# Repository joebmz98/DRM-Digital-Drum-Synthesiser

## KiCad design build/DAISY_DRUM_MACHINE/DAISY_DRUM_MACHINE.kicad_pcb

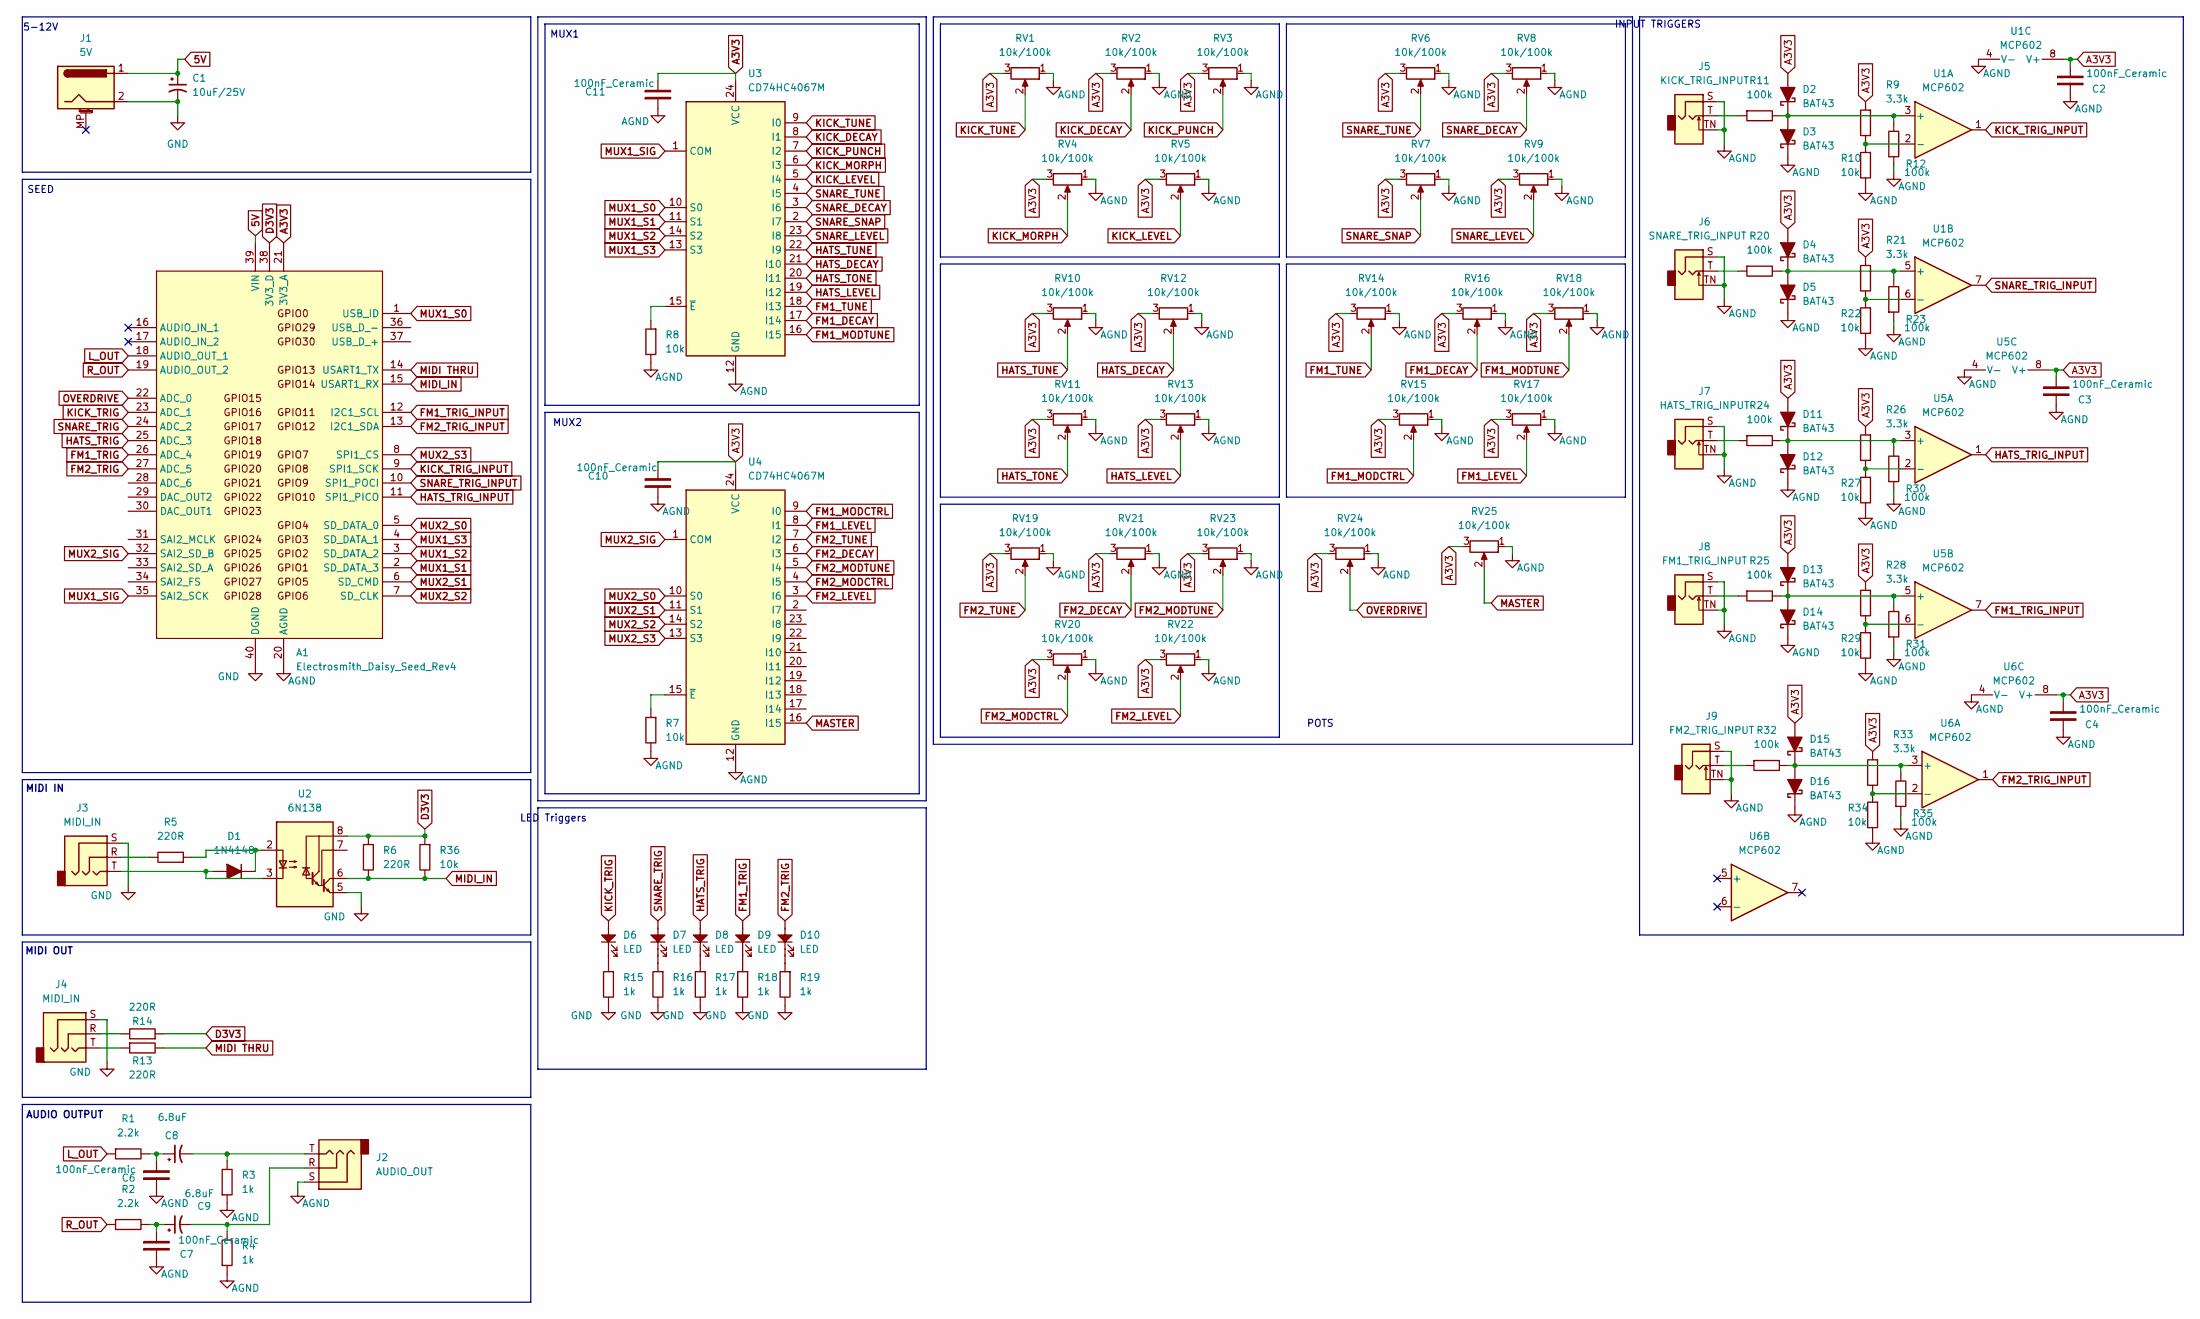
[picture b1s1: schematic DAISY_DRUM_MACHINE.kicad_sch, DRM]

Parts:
A1: Electrosmith_Daisy_Seed_Rev4; Electrosmith_Daisy_Seed
C1: 10uF_4x5.3_10V; CP_Radial_D4.0mm_P1.50mm; Part Number EEE-FN1A100R; JLCPCB ID C176661
C2, C3, C4, C6, C7, C10, C11: 100nF_Ceramic; C_0603_1608Metric_Pad1.08x0.95mm_HandSolder
C8, C9: 6.8uF; CP_Radial_D4.0mm_P1.50mm; Part Number EEE-FN1A100R; JLCPCB ID C176661
D1: 1N4148; D_0603_1608Metric_Pad1.05x0.95mm_HandSolder
D2, D3, D4, D5, D11, D12, D13, D14, D15, D16: BAT43; D_DO-35_SOD27_P7.62mm_Horizontal
D6, D7, D8, D9, D10: LED; LED_D5.0mm
J1: 5V; BarrelJack_GCT_DCJ200-10-A_Horizontal
J2: AUDIO_OUT; Jack_3.5mm_CUI_SJ1-3525N_Horizontal
J3, J4: MIDI_IN; Jack_3.5mm_CUI_SJ1-3525N_Horizontal
J5: KICK_TRIG_INPUT; Jack_3.5mm_CUI_SJ1-3525N_Horizontal
J6: SNARE_TRIG_INPUT; Jack_3.5mm_CUI_SJ1-3525N_Horizontal
J7: HATS_TRIG_INPUT; Jack_3.5mm_CUI_SJ1-3525N_Horizontal
J8: FM1_TRIG_INPUT; Jack_3.5mm_CUI_SJ1-3525N_Horizontal
J9: FM2_TRIG_INPUT; Jack_3.5mm_CUI_SJ1-3525N_Horizontal
R1, R2: 2.2k; R_0603_1608Metric_Pad0.98x0.95mm_HandSolder
R3, R4, R15, R16, R17, R18, R19: 1k; R_0603_1608Metric_Pad0.98x0.95mm_HandSolder
R5, R6, R13, R14: 220R; R_0603_1608Metric_Pad0.98x0.95mm_HandSolder
R7, R8, R10, R22, R27, R29, R34, R36: 10k; R_0603_1608Metric_Pad0.98x0.95mm_HandSolder
R9, R21, R26, R28, R33: 3.3k; R_0603_1608Metric_Pad0.98x0.95mm_HandSolder
R11, R12, R20, R23, R24, R25, R30, R31, R32, R35: 100k; R_0603_1608Metric_Pad0.98x0.95mm_HandSolder
RV1, RV2, RV3, RV4, RV5, RV6, RV7, RV8, RV9, RV10, RV11, RV12, RV13, RV14, RV15, RV16, RV17, RV18, RV19, RV20, RV21, RV22, RV23, RV24, RV25: 10k/100k; Potentiometer_Alpha_RD901F-40-00D_Single_Vertical
U1, U5, U6: MCP602; SOIC-8_3.9x4.9mm_P1.27mm
U2: 6N138; DIP-8_W7.62mm_LongPads
U3, U4: CD74HC4067M; SOIC-24W_7.5x15.4mm_P1.27mm

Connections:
5V: A1.39 (VIN), C1.1, J1.1
A3V3: A1.21 (3V3_A), C2.2, C3.2, C4.2, C10.2, C11.2, D2.2 (A), D4.2 (A), D11.2 (A), D13.2 (A), D15.2 (A), R9.1, R21.1, R26.1, R28.1, R33.1, RV1.3, RV2.3, RV3.3, RV4.3, RV5.3, RV6.3, RV7.3, RV8.3, RV9.3, RV10.3, RV11.3, RV12.3, RV13.3, RV14.3, RV15.3, RV16.3, RV17.3, RV18.3, RV19.3, RV20.3, RV21.3, RV22.3, RV23.3, RV24.3, RV25.3, U1.8 (V+), U3.24 (VCC), U4.24 (VCC), U5.8 (V+), U6.8 (V+)
AGND: A1.20 (AGND), C2.1, C3.1, C4.1, C6.1, C7.1, C10.1, C11.1, D3.1 (K), D5.1 (K), D12.1 (K), D14.1 (K), D16.1 (K), J2.S, J5.S, J5.TN, J6.S, J6.TN, J7.S, J7.TN, J8.S, J8.TN, J9.S, J9.TN, R3.1, R4.1, R7.2, R8.2, R10.2, R12.1, R22.2, R23.1, R27.2, R29.2, R30.1, R31.1, R34.2, R35.1, RV1.1, RV2.1, RV3.1, RV4.1, RV5.1, RV6.1, RV7.1, RV8.1, RV9.1, RV10.1, RV11.1, RV12.1, RV13.1, RV14.1, RV15.1, RV16.1, RV17.1, RV18.1, RV19.1, RV20.1, RV21.1, RV22.1, RV23.1, RV24.1, RV25.1, U1.4 (V-), U3.12 (GND), U4.12 (GND), U5.4 (V-), U6.4 (V-)
D3V3: A1.38 (3V3_D), R6.1, R14.1, R36.1, U2.8 (VCC)
FM1_DECAY: RV16.2, U3.17 (I14)
FM1_LEVEL: RV17.2, U4.8 (I1)
FM1_MODCTRL: RV15.2, U4.9 (I0)
FM1_MODTUNE: RV18.2, U3.16 (I15)
FM1_TRIG: A1.26 (ADC_4), D9.2
FM1_TRIG_INPUT: A1.12 (I2C1_SCL), U5.7
FM1_TUNE: RV14.2, U3.18 (I13)
FM2_DECAY: RV21.2, U4.6 (I3)
FM2_LEVEL: RV22.2, U4.3 (I6)
FM2_MODCTRL: RV20.2, U4.4 (I5)
FM2_MODTUNE: RV23.2, U4.5 (I4)
FM2_TRIG: A1.27 (ADC_5), D10.2
FM2_TRIG_INPUT: A1.13 (I2C1_SDA), U6.1
FM2_TUNE: RV19.2, U4.7 (I2)
GND: A1.40 (DGND), C1.2, J1.2, J3.S, J4.S, R15.2, R16.2, R17.2, R18.2, R19.2, U2.5 (GND)
HATS_DECAY: RV12.2, U3.21 (I10)
HATS_LEVEL: RV13.2, U3.19 (I12)
HATS_TONE: RV11.2, U3.20 (I11)
HATS_TRIG: A1.25 (ADC_3), D8.2
HATS_TRIG_INPUT: A1.11 (SPI1_PICO), U5.1
HATS_TUNE: RV10.2, U3.22 (I9)
KICK_DECAY: RV2.2, U3.8 (I1)
KICK_LEVEL: RV5.2, U3.5 (I4)
KICK_MORPH: RV4.2, U3.6 (I3)
KICK_PUNCH: RV3.2, U3.7 (I2)
KICK_TRIG: A1.23 (ADC_1), D6.2
KICK_TRIG_INPUT: A1.9 (SPI1_SCK), U1.1
KICK_TUNE: RV1.2, U3.9 (I0)
L_OUT: A1.18 (AUDIO_OUT_1), R1.1
MASTER: RV25.2, U4.16 (I15)
MIDI THRU: A1.14 (USART1_TX), R13.2
MIDI_IN: A1.15 (USART1_RX), R6.2, R36.2, U2.6 (VO2)
MUX1_S0: A1.1 (USB_ID), U3.10 (S0)
MUX1_S1: A1.2 (SD_DATA_3), U3.11 (S1)
MUX1_S2: A1.3 (SD_DATA_2), U3.14 (S2)
MUX1_S3: A1.4 (SD_DATA_1), U3.13 (S3)
MUX1_SIG: A1.35 (SAI2_SCK), U3.1 (COM)
MUX2_S0: A1.5 (SD_DATA_0), U4.10 (S0)
MUX2_S1: A1.6 (SD_CMD), U4.11 (S1)
MUX2_S2: A1.7 (SD_CLK), U4.14 (S2)
MUX2_S3: A1.8 (SPI1_CS), U4.13 (S3)
MUX2_SIG: A1.32 (SAI2_SD_B), U4.1 (COM)
unnamed: C6.2, C8.1, R1.2
unnamed: C7.2, C9.1, R2.2
unnamed: C8.2, J2.T, R3.2
unnamed: C9.2, J2.R, R4.2
unnamed: D1.2 (A), J3.T, U2.3 (C2)
unnamed: D1.1 (K), R5.1, U2.2 (C1)
unnamed: D2.1 (K), D3.2 (A), R11.2, R12.2, U1.3 (+)
unnamed: D4.1 (K), D5.2 (A), R20.2, R23.2, U1.5 (+)
unnamed: D6.1, R15.1
unnamed: D7.1, R16.1
unnamed: D8.1, R17.1
unnamed: D9.1, R18.1
unnamed: D10.1, R19.1
unnamed: D11.1 (K), D12.2 (A), R24.2, R30.2, U5.3 (+)
unnamed: D13.1 (K), D14.2 (A), R25.2, R31.2, U5.5 (+)
unnamed: D15.1 (K), D16.2 (A), R32.2, R35.2, U6.3 (+)
unnamed: J3.R, R5.2
unnamed: J4.R, R14.2
unnamed: J4.T, R13.1
unnamed: J5.T, R11.1
unnamed: J6.T, R20.1
unnamed: J7.T, R24.1
unnamed: J8.T, R25.1
unnamed: J9.T, R32.1
unnamed: R9.2, R10.1, U1.2 (-)
unnamed: R21.2, R22.1, U1.6 (-)
unnamed: R8.1, U3.15 (~E)
unnamed: R7.1, U4.15 (~E)
unnamed: R26.2, R27.1, U5.2 (-)
unnamed: R28.2, R29.1, U5.6 (-)
unnamed: R33.2, R34.1, U6.2 (-)
OVERDRIVE: A1.22 (ADC_0), RV24.2
R_OUT: A1.19 (AUDIO_OUT_2), R2.1
SNARE_DECAY: RV8.2, U3.3 (I6)
SNARE_LEVEL: RV9.2, U3.23 (I8)
SNARE_SNAP: RV7.2, U3.2 (I7)
SNARE_TRIG: A1.24 (ADC_2), D7.2
SNARE_TRIG_INPUT: A1.10 (SPI1_POCI), U1.7
SNARE_TUNE: RV6.2, U3.4 (I5)

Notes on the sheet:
MUX1
MIDI IN
LED Triggers
AUDIO OUTPUT
SEED
INPUT TRIGGERS
MUX2
MIDI OUT
5-12V
POTS

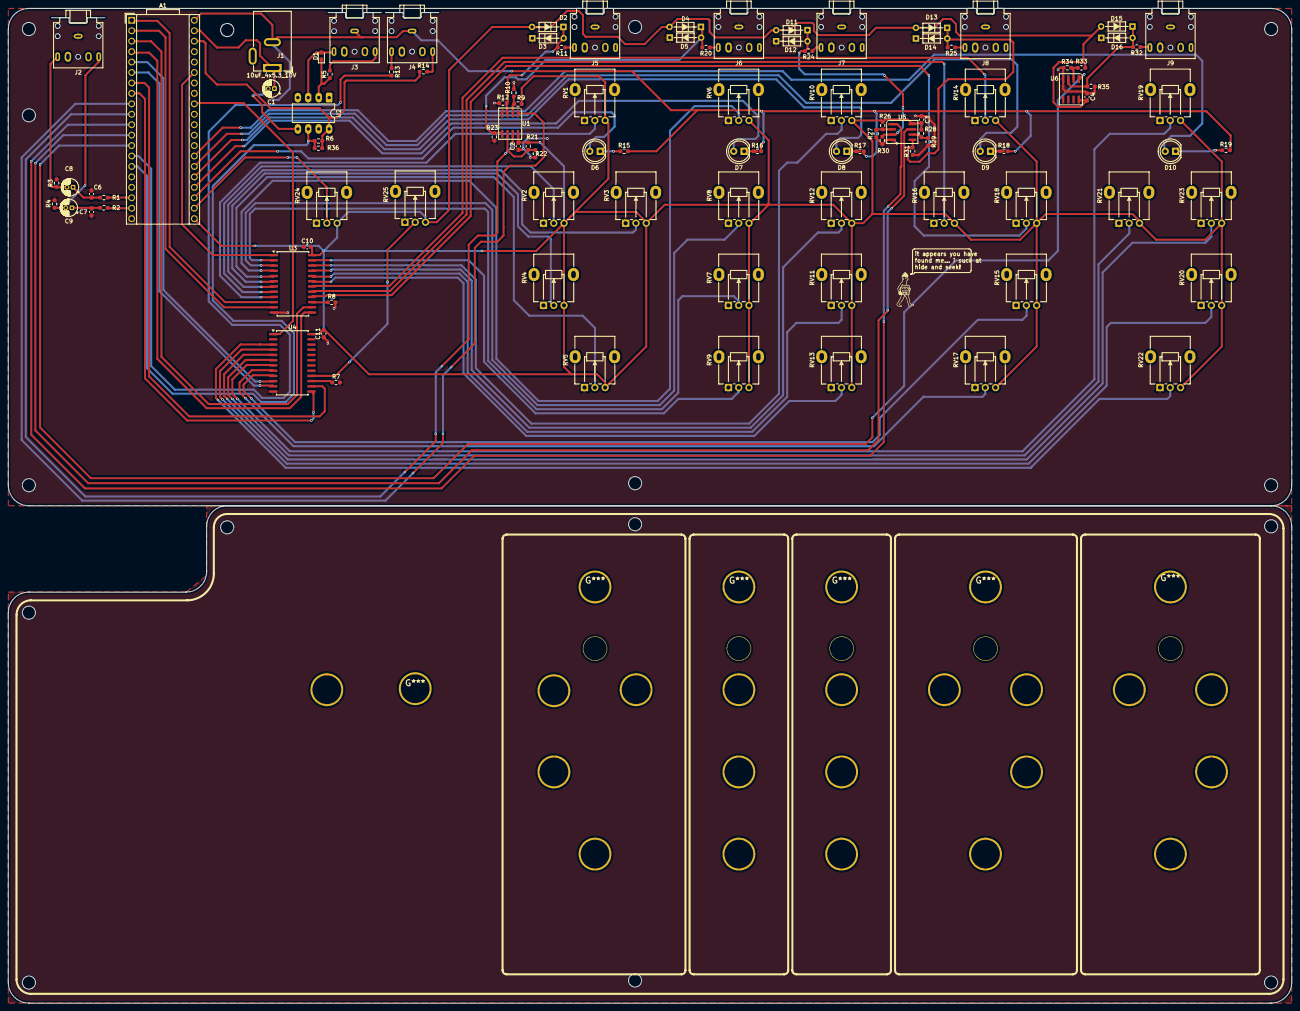
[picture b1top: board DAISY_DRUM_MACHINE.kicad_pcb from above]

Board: 2 copper layers, 312.2 x 242.0 mm, 103 parts (0 on the bottom side), 85 nets.

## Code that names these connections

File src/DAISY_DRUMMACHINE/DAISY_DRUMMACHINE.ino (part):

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
// MUX PINS
// MUX 1 -- S & SIG --
#define MUX1_S0 0
#define MUX1_S1 1
#define MUX1_S2 2
#define MUX1_S3 3
#define MUX1_SIG A11
// MUX 2 -- S & SIG --
#define MUX2_S0 4
#define MUX2_S1 5
#define MUX2_S2 6
#define MUX2_S3 7
#define MUX2_SIG A10

// MUX 1 CHANNEL DEFINITIONS
#define KICK_TUNE 0
#define KICK_DECAY 1
#define KICK_PUNCH 2
#define KICK_MORPH 3
#define KICK_LEVEL 4
#define SNARE_TUNE 5
#define SNARE_DECAY 6
#define SNARE_SNAP 7
#define SNARE_LEVEL 8
#define HATS_TUNE 9
#define HATS_DECAY 10
#define HATS_TONE 11
#define HATS_LEVEL 12
#define FM1_CARRIER_TUNE 13
#define FM1_DECAY 14
#define FM1_MODULATOR_TUNE 15

// MUX 2 CHANNEL DEFINITIONS
#define FM1_MOD_AMOUNT 0
#define FM1_LEVEL 1
#define FM2_CARRIER_TUNE 2
#define FM2_DECAY 3
#define FM2_MODULATOR_TUNE 4
#define FM2_MOD_AMOUNT 5
#define FM2_LEVEL 6
//#define SNARE_SNAP 7
//#define SNARE_LEVEL 8
//#define HATS_TUNE 9
//#define HATS_DECAY 10
//#define HATS_TONE 11
//#define HATS_LEVEL 12
//#define FM1_CARRIER_TUNE 13
//#define FM1_DECAY 14
#define MASTER_VOLUME 15

// TRIGGER/LED PINS
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
  // Setup MUX control pins as outputs
  // MUX 1
  pinMode(MUX1_S0, OUTPUT);
  pinMode(MUX1_S1, OUTPUT);
  pinMode(MUX1_S2, OUTPUT);
  pinMode(MUX1_S3, OUTPUT);
  pinMode(MUX1_SIG, INPUT);
  // MUX 2
  pinMode(MUX2_S0, OUTPUT);
  pinMode(MUX2_S1, OUTPUT);
  pinMode(MUX2_S2, OUTPUT);
  pinMode(MUX2_S3, OUTPUT);
  pinMode(MUX2_SIG, INPUT);

  // Setup direct pot pin
  pinMode(DISTORTION_POT, INPUT);
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void processValues() {

  // KICK POTS
  kickOscTune = fmap(muxValues[KICK_TUNE] / 65535.0f, 30.0, 120.0, Mapping::EXP);
  kickEnvDecay = fmap(muxValues[KICK_DECAY] / 65535.0f, 0.01, 1.5, Mapping::EXP);
  kickPunch = muxValues[KICK_PUNCH] / 65535.0f;  // 0.0 TO 1.0f
  kickMorph = muxValues[KICK_MORPH] / 65535.0f;  // 0.0 TO 1.0f
  kickLevel = fmap(muxValues[KICK_LEVEL] / 65535.0f, 0.0, 1.0, Mapping::LINEAR);

  // SNARE POTS
  snareTune = fmap(muxValues[SNARE_TUNE] / 65535.0f, 180.0, 350.0, Mapping::EXP);
  snareDecay = fmap(muxValues[SNARE_DECAY] / 65535.0f, 0.05, 1.5, Mapping::EXP);
  snareSnapDecay = fmap(muxValues[SNARE_SNAP] / 65535.0f, 0.05, 1.8, Mapping::EXP);
  snareLevel = fmap(muxValues[SNARE_LEVEL] / 65535.0f, 0.0, 1.0, Mapping::LINEAR);

  // HATS POTS
  hatsBaseTune = fmap(muxValues[HATS_TUNE] / 65535.0f, 250.0, 500.0, Mapping::EXP);
  hatsDecay = fmap(muxValues[HATS_DECAY] / 65535.0f, 0.01, 0.8, Mapping::EXP);
  hatsTone = fmap(muxValues[HATS_TONE] / 65535.0f, 0.0, 1.0, Mapping::LINEAR);
  hatsLevel = fmap(muxValues[HATS_LEVEL] / 65535.0f, 0.0, 1.0, Mapping::LINEAR);

  // FM1 POTS
  fm1Tune = fmap(muxValues[FM1_CARRIER_TUNE] / 65535.0f, 100.0, 600.0, Mapping::EXP);
  fm1Decay = fmap(muxValues[FM1_DECAY] / 65535.0f, 0.05, 1.0, Mapping::EXP);
  fm1ModTune = fmap(muxValues[FM1_MODULATOR_TUNE] / 65535.0f, 120.0, 1000.0, Mapping::EXP);
  fm1Level = fmap(mux2Values[FM1_LEVEL] / 65535.0f, 0.0, 1.0, Mapping::LINEAR);
  fm1ModCtrl = mux2Values[FM1_MOD_AMOUNT] / 65535.0f;

  if (fm1ModCtrl < 0.01f) {
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
  // FM2 POTS
  fm2Tune = fmap(mux2Values[FM2_CARRIER_TUNE] / 65535.0f, 100.0, 800.0, Mapping::EXP);
  fm2Decay = fmap(mux2Values[FM2_DECAY] / 65535.0f, 0.05, 1.5, Mapping::EXP);
  fm2ModTune = fmap(mux2Values[FM2_MODULATOR_TUNE] / 65535.0f, 120.0, 1000.0, Mapping::EXP);
  fm2Level = fmap(mux2Values[FM2_LEVEL] / 65535.0f, 0.0, 1.0, Mapping::LINEAR);
  fm2ModCtrl = mux2Values[FM2_MOD_AMOUNT] / 65535.0f;

  if (fm2ModCtrl < 0.01f) {
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
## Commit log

2026-03-25 DRM_mk1
2026-04-21 firmware update
    improved midi
2026-04-23 pcb updates
2026-04-23 Schematic & PCB update
    Added drum voice inputs with circuit protection
